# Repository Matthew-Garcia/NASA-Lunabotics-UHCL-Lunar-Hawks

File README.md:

> **New simulation review branch:** [Full rover CAD, Gazebo/RViz launch and KiCad Rev C](docs/SIMULATION_REVIEW.md). Reference-derived geometry; runtime and electrical review remain pending.

# NASA Lunabotics · UHCL Lunar Hawks

### Proof-of-concept lunar excavation rover
Embedded systems · ROS 2 · micro-ROS · OpenCV · LiDAR · Gazebo · Hardware integration

A University of Houston–Clear Lake student and research rover project for lunar-regolith excavation, collection, transportation, and disposal.

This repository brings together the Lunar Hawks rover's ESP32 firmware, NVIDIA Jetson ROS 2 software, micro-ROS communication, mechanical models, electrical documentation, Gazebo simulation assets, and ongoing autonomous-navigation development.

**Status: prototype / research.** Physical rover subsystems have been demonstrated, while the newly added autonomous mission software and simulation environment remain development implementations requiring integration and validation on the physical rover.

This is a team-member-maintained academic/research repository and is **not a NASA-owned or NASA-endorsed software release**.

[ROS 2](ros2_ws/README.md) ·
[micro-ROS](firmware/micro_ros/README.md) ·
[MicroPython](firmware/micropython/README.md) ·
[Autonomy](ros2_ws/src/lunabotics_autonomy/) ·
[Gazebo Simulation](simulation/) ·
[CAD](cad/) ·
[Control PCB](hardware/rover_control_pcb/README.md) ·
[Research](docs/publication/README.md) ·
[Testing](docs/testing/README.md)

---

## Project objectives

The Lunar Hawks rover is being developed as a proof-of-concept robotic platform for lunar excavation research.

The overall mission architecture is intended to support:

1. Entering a simulated or competition excavation environment.
2. Navigating using LiDAR and camera sensing.
3. Identifying traversable regolith terrain.
4. Operating the front bucket-ladder / conveyor excavation mechanism.
5. Transporting collected material.
6. Detecting the disposal area using computer vision.
7. Identifying the four goal-post features surrounding the disposal zone.
8. Aligning the rover with the goal.
9. Activating the disposal bucket.
10. Returning to navigation or excavation behavior.

The current autonomous software is a development baseline rather than a fully validated competition autonomy stack.

---

## Demonstration and evidence

[Watch the archived Gazebo simulation clip](media/Gazebo_Sim.mp4) ·
[Original software documentation](docs/legacy/UHCL_NASA_Lunabotics_Rover_Software_Documentation.pdf)

The physical rover project has demonstrated subsystem functionality including:

- Forward and reverse mobility
- Differential-drive turning
- Wireless teleoperation
- Conveyor / bucket-ladder operation
- Material transportation
- Disposal-bucket actuation
- Jetson-to-ESP32 communication
- micro-ROS integration
- LiDAR integration
- Camera integration

These historical demonstrations do **not** automatically validate the newly added autonomy, Gazebo, CAD, or electrical-development files.

Physical test videos, measured results, software revisions, and dated validation records should continue to be added to the [testing evidence register](docs/testing/README.md).

| Area | Included here | Verification status |
| --- | --- | --- |
| ESP32 micro-ROS | Original C firmware and integration metadata | Preserved project source; hardware revalidation recommended |
| Jetson ROS 2 | Teleoperation and controller software | Existing architecture; environment validation ongoing |
| OpenCV vision | Goal-post and regolith detection nodes | Development baseline; physical threshold tuning required |
| LiDAR autonomy | Front-obstacle safety node | Implemented baseline; rover testing required |
| Mission control | Autonomous excavation/transport/disposal state machine | Implemented baseline; not yet a demonstrated full autonomous mission |
| Gazebo simulation | Lunabotics arena world and rover model | Source added; integrated launch and runtime validation still required |
| Mechanical CAD | Original rover STLs plus autonomy-development CAD | New models are reference/development geometry |
| Rover wheel | 304.8 mm × 100 mm conceptual wheel with 12 grousers | Parametric recreation; hub dimensions must be verified before fabrication |
| Rover control PCB | Routed 4-layer KiCad 9 ESP32/CAN design with USB programming and safety/inhibit logic | ERC/DRC clean; pending fabrication and bring-up |
| Electrical Rev B | Architecture recommendations and schematic review | Engineering-development documentation |
| Research | Manuscript/project documentation | Research publication workflow ongoing |

---

# System architecture

```mermaid
flowchart TD

    Controller["Xbox / Game Controller"] --> Jetson["NVIDIA Jetson Orin NX"]

    Camera["RGB / Depth Camera"] --> Jetson
    Lidar["RPLIDAR"] --> Jetson

    Jetson --> ROS["ROS 2 Humble"]

    ROS --> Teleop["Teleoperation"]
    ROS --> Vision["OpenCV Perception"]
    ROS --> Navigation["Navigation / Mission Logic"]
    ROS --> Safety["LiDAR Safety"]

    Vision --> Mission["Autonomous Mission Manager"]
    Navigation --> Mission
    Safety --> Mission

    Mission --> CMD["/cmd_vel"]
    Teleop --> CMD

    CMD --> Agent["micro-ROS Agent"]

    Agent -->|"UART 115200"| ESP32["ESP32"]

    ESP32 --> WheelDrivers["Wheel Motor Controllers"]
    ESP32 --> Excavator["Excavation Actuators"]
    ESP32 --> Dump["Disposal Bucket Actuators"]

    WheelDrivers --> Wheels["Four Drive Motors"]
    Excavator --> Conveyor["Bucket-Ladder / Conveyor"]
    Dump --> Bucket["Regolith Disposal Bucket"]
```

The architecture separates high-level robotics computation from low-level actuator control.

### NVIDIA Jetson

The Jetson is responsible for higher-level robotics functions such as:

- ROS 2
- Computer vision
- LiDAR processing
- Mapping and localization
- Navigation
- Mission coordination
- Future autonomous excavation behavior

### ESP32

The ESP32 provides hardware-facing embedded control including:

- Motor command generation
- PWM
- Direction control
- Actuator control
- micro-ROS communication
- Hardware safety behavior

The deployed ESP32-WROOM implementation and any future ESP32-S3 control PCB should **not be assumed to be pin-compatible or firmware-compatible without verification**.

---

# Autonomous mission development

The repository now contains an experimental ROS 2 autonomy package:

```text
ros2_ws/src/lunabotics_autonomy/
```

Major nodes include:

### Goal-post detector

```text
goal_post_detector.py
```

Uses OpenCV image processing to locate vertical goal-post candidates from the camera stream.

Publishes goal information that can be used to center the rover between the visible posts.

Development topics include:

```text
/vision/goal_posts/target
/vision/goal_posts/count
/vision/goal_posts/debug
```

The current detector uses configurable image-processing thresholds intended primarily as a simulation and development baseline.

---

### Regolith detector

```text
regolith_detector.py
```

Provides a preliminary OpenCV terrain-classification method for identifying regolith-like regions.

The current implementation is intentionally simple and should eventually be replaced or supplemented with perception trained and tested using representative lunar-regolith imagery.

---

### LiDAR safety

```text
lidar_safety.py
```

Processes `/scan` data and monitors the forward sector of the rover.

It can issue an obstacle-stop condition if an object is detected inside the configured safety distance.

Example topics:

```text
/safety/obstacle_stop
/safety/front_clearance
```

---

### Mission manager

```text
mission_manager.py
```

Implements a development state machine:

```text
ENTER
  ↓
SEARCH_REGOLITH
  ↓
EXCAVATE
  ↓
SEARCH_GOAL
  ↓
ALIGN_GOAL
  ↓
DUMP
  ↓
DONE
```

The mission manager can command:

```text
/cmd_vel
/excavator/enable
/bucket/dump
```

These outputs are intended to eventually interface with the existing ESP32 / micro-ROS hardware layer.

---

# Gazebo simulation

A Lunabotics-inspired Gazebo development environment is included under:

```text
simulation/worlds/
```

Current world:

```text
lunabotics_arena.world
```

The environment contains:

- Excavation terrain
- Arena boundaries
- Disposal region
- Four visual goal posts
- A simplified mission layout

The environment is a **development approximation**, not a claim of exact NASA competition-field dimensions.

A simplified rover model is also included:

```text
ros2_ws/src/lunabotics_description/urdf/lunabotics_rover.urdf.xacro
```

It represents:

- Four-wheel differential drive
- Rover chassis
- Front excavation conveyor
- Rear disposal bucket
- LiDAR
- RGB camera

An integrated Gazebo spawn/bringup launch file is still planned.

*Lunar Hawks rover simulation with grouser wheels, a scoop conveyor excavator, and an actuator-driven disposal bucket. Full autonomous excavation and disposal remain under development.*

---

# Computer vision

The autonomy software uses OpenCV as a development perception layer.

Current objectives include:

```text
Camera
   ↓
OpenCV
   ↓
Goal-post detection
   ↓
Four-post confirmation
   ↓
Goal-center calculation
   ↓
Rover alignment
   ↓
Dump sequence
```

Future work may combine camera information with LiDAR geometry for more robust goal detection and navigation.

---

# LiDAR navigation

LiDAR provides the geometric sensing layer for autonomous rover development.

Planned progression:

```text
LiDAR
  ↓
Obstacle detection
  ↓
Localization
  ↓
Mapping
  ↓
Nav2 costmaps
  ↓
Waypoint navigation
  ↓
Mission navigation
```

Future integration is expected to include ROS 2 Nav2 and/or SLAM Toolbox.

---

# Mechanical development

The repository includes both preserved project CAD and new development geometry.

```text
cad/
```

The original supplied meshes remain directly in `cad/`. Generated geometry is separated by purpose:

```text
cad/
├── original supplied STL files
├── full_rover/
│   ├── chassis, bucket and excavator parts
│   ├── ESP32 and Jetson enclosures
│   └── 248 mm and 300 mm wheel variants
└── autonomy_rover/
    ├── goal_post.scad / .stl
    ├── grouser_wheel_12_short.scad / .stl
    └── rover_chassis_simplified.scad / .stl
```

The full-rover wheel set and printable cover variants are documented in [`cad/full_rover/WHEEL.md`](cad/full_rover/WHEEL.md).

## Grouser wheel

The development wheel is based on documented rover dimensions:

- Diameter: **304.8 mm**
- Width: **100 mm**
- Grousers: **12**
- Equal angular spacing: **30°**

The grouser projection in this development model was shortened relative to the initial generated geometry.

The wheel STL is **not fabrication-authoritative**. Hub diameter, shaft bore, bolt-circle dimensions, materials, tolerances, and drivetrain interfaces must be verified against the physical rover.

---

# Electrical architecture

The rover uses separated high-current motor and computing power domains.

```mermaid
flowchart TD

    BAT24["24 V Battery"] --> Fuse["Main Fuse"]
    Fuse --> Estop["Latching E-Stop / Contactor"]
    Estop --> Dist["Fused 24 V Distribution"]

    Dist --> FL["Front Left Motor Controller"]
    Dist --> FR["Front Right Motor Controller"]
    Dist --> RL["Rear Left Motor Controller"]
    Dist --> RR["Rear Right Motor Controller"]
    Dist --> EX["Excavator / Conveyor"]
    Dist --> ACT["Linear Actuators"]

    VMOUNT["V-Mount Compute Battery"] --> JetsonFuse["Compute Fuse / Protection"]
    JetsonFuse --> Jetson["Jetson Orin NX"]

    Logic["Regulated Logic Rail"] --> ESP32["ESP32"]
    Logic --> Sensors["Low-Voltage Sensors"]

    Jetson <-->|"UART / micro-ROS"| ESP32
```

Rev-B design recommendations are located in:

```text
docs/electrical/rev_b/
```

They include:

- Main battery protection
- Branch fusing
- Emergency-stop architecture
- Transient suppression
- Power-domain separation
- Logic-rail decoupling
- UART signal protection
- Test points
- Current-monitoring recommendations
- Motor-controller schematic review

One important design-review item is ensuring that schematic symbols and labels accurately represent the physical motor controllers being used.

---

# Start with software-only checks

Clone the repository:

```bash
git clone https://github.com/Matthew-Garcia/NASA-Lunabotics-UHCL-Lunar-Hawks.git

cd NASA-Lunabotics-UHCL-Lunar-Hawks
```

Run MicroPython protocol tests:

```bash
python3 firmware/micropython/test.py
```

Run repository tests:

```bash
python3 -m unittest discover -s tests -v
```

For ROS 2 setup, see:

[ROS 2 workspace instructions](ros2_ws/README.md)

For micro-ROS integration:

[micro-ROS notes](firmware/micro_ros/README.md)

Before powering physical motors or actuators:

[Electrical safety checklist](docs/electrical/SAFETY.md)

---

# Repository map

| Path | Purpose |
| --- | --- |
| `firmware/micro_ros/` | ESP32 C / micro-ROS firmware |
| `firmware/micropython/` | MicroPython communication prototype |
| `ros2_ws/src/lunabotics_teleop/` | ROS 2 controller and teleoperation package |
| `ros2_ws/src/lunabotics_autonomy/` | OpenCV, LiDAR, and autonomous mission development |
| `ros2_ws/src/lunabotics_description/` | Rover URDF/Xacro description |
| `simulation/worlds/` | Gazebo Lunabotics arena |
| `hardware/rover_control_pcb/` | Proposed rover-control/interface PCB |
| `cad/` | Mechanical models and original STL files |
| `cad/full_rover/` | Full rover reconstruction, excavator, bucket, enclosures and wheel variants |
| `cad/autonomy_rover/` | Earlier simplified autonomy-development CAD and goal-post geometry |
| `docs/architecture/` | Interfaces, command semantics, and system architecture |
| `docs/electrical/` | Electrical safety and architecture documentation |
| `docs/electrical/rev_b/` | Rev-B electrical recommendations and schematic review |
| `docs/testing/` | Evidence register and validation planning |
| `docs/publication/` | Research publication status |
| `docs/legacy/` | Original software documentation |
| `media/` | Rover images, team media, and Gazebo video |
| `tests/` | Host-side software tests |

---

# Development roadmap

- [x] Integrate Jetson and ESP32 architecture.
- [x] Establish ROS 2 teleoperation.
- [x] Establish micro-ROS communication.
- [x] Integrate LiDAR hardware.
- [x] Integrate camera hardware.
- [x] Demonstrate rover mobility.
- [x] Demonstrate excavation conveyor operation.
- [x] Demonstrate disposal-bucket actuation.
- [x] Add OpenCV goal-post detection baseline.
- [x] Add regolith-vision development node.
- [x] Add LiDAR obstacle-safety node.
- [x] Add autonomous mission state-machine baseline.
- [x] Add Gazebo Lunabotics arena source.
- [x] Add simplified rover URDF/Xacro.
- [x] Add 12-grouser wheel development CAD.
- [x] Add Rev-B electrical architecture review.
- [ ] Complete ROS package for rover description and Gazebo spawning.
- [ ] Add combined simulation launch file.
- [ ] Integrate ROS 2 Nav2.
- [ ] Integrate SLAM / localization.
- [ ] Fuse camera and LiDAR perception.
- [ ] Validate four-post detection using representative physical targets.
- [ ] Validate autonomous navigation on the physical rover.
- [ ] Integrate autonomous excavation control with ESP32 firmware.
- [ ] Implement mission recovery and watchdog behavior.
- [ ] Record quantitative excavation and navigation results.
- [ ] Complete and independently review production PCB schematic/layout.
- [ ] Demonstrate a complete autonomous excavation → transport → disposal mission.

---

# Research

**Matthew Garcia**  
Repository maintainer · Robotics systems integration · Embedded systems · ROS 2 / autonomy contributor · Co-Author

**Dr. Luong Nguyen, Ph.D.**  
Research adviser · Lead-Author

Credit also belongs to the **University of Houston–Clear Lake Lunar Hawks team** and the students who designed, built, tested, and improved the rover platform.

Research project:

*Design and Implementation of a Proof-of-Concept Excavating Rover Platform for Lunar Regolith Collection and Transportation*

The project has been accepted for presentation at **ISMCR 2026 — International Symposium on Measurement and Control in Robotics**.

Research documentation and publication status are maintained under:

[Read the author manuscript (Word)](docs/publication/manuscript/Nguyen_Garcia_ISMCR2026_Final_Revision.docx) · [Publication status](docs/publication/README.md)

---

## Links

[Matthew Garcia Portfolio](https://matthew-garcia-portfolio.vercel.app/) ·
[LinkedIn](https://www.linkedin.com/in/matthew-garcia-165634195/) ·
[Original UHCL Lunar Hawks Repository](https://github.com/Matthew-Garcia/uhcl-lunar-hawks-lunabotics)

---

# Safety

This repository contains software and design material capable of controlling motors and electromechanical actuators.

Do not connect development software directly to powered hardware without verifying:

- Emergency stop functionality
- Motor-controller pin assignments
- PWM ranges
- Direction logic
- Current limits
- Fuse ratings
- Mechanical clearance
- Command timeout behavior
- Communication-loss behavior

See:

[Electrical Safety](docs/electrical/SAFETY.md)

---

# License and provenance

The original MIT license is retained.

See [NOTICE](NOTICE.md) for source revision, provenance, and rights information.

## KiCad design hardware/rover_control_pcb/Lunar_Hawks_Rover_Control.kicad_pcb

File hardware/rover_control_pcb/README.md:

# NASA Lunabotics — UHCL Lunar Hawks Low-Level Embedded Control & I/O PCB

**Native KiCad 9.0 rover-control hardware design** for the University of Houston–Clear Lake Lunar Hawks Lunabotics rover.

This board is the rover's **low-level embedded control and I/O PCB**. The NVIDIA Jetson Orin NX remains the high-level ROS 2/autonomy computer, while this PCB handles the hardware-facing embedded layer: ESP32 control, CAN communication, programming/service I/O, safety/inhibit logic, and command interfaces to external wheel and mechanism drivers.

> **Engineering draft — not released for fabrication or powered operation.** ERC/DRC results establish design-file consistency, not electrical, thermal, RF, EMC, harness, or safety qualification.

## Designed in KiCad 9.0

The controller is designed and maintained **natively in KiCad 9.0**. The current design snapshot was validated with the KiCad 9 toolchain.

The KiCad project includes the project file, hierarchical schematic sheets, routed PCB layout, local symbol resources, 3D-model support, board artwork, BOM/component records, placement data, layout notes, and electrical validation reports.

## Rover control hierarchy

```text
NVIDIA Jetson Orin NX
High-level ROS 2 / autonomy / perception / planning
                 |
                 | CAN / system interface
                 v
LOW-LEVEL EMBEDDED CONTROL & I/O PCB
ESP32 / safety logic / command generation / hardware I/O
                 |
                 v
External motor drivers / actuators / excavation / disposal
```

The board silkscreen identifies the design as:

- **NASA LUNABOTICS — UHCL LUNAR HAWKS**
- **LOW-LEVEL EMBEDDED CONTROL & I/O PCB**
- **CONTROL SIGNALS ONLY — NO MOTOR POWER**

## Current board

- 160 × 100 mm working outline
- four copper layers
- blue solder mask / white silkscreen configuration
- ESP32-WROOM-32E-N4 embedded controller module
- USB-C programming/service interface
- Classical CAN interface with two parallel connectors and selectable 120 Ω termination
- four external BLDC wheel-driver command interfaces
- external linear-actuator / excavation / deployment / disposal command interfaces
- protected controller power conversion to 5 V and 3.3 V rails
- watchdog, re-arm, command-enable, and inhibit logic
- provisional wheel-stop request interfaces
- system/status indicators and service headers
- four mounting holes and Lunar Hawks board artwork
- **motor-current paths remain external to the PCB**

## Architecture notes

**Embedded controller:** the ESP32 provides the low-level hardware-control layer. Manual BOOT/reset support and the USB programming path are integrated on the board.

**CAN:** the controller-side CAN node includes the transceiver, protection, parallel bus connectors, and selectable termination. The Jetson requires its own appropriate CAN transceiver/adapter; logic-level CAN signals are not connected directly to CAN_H/CAN_L.

**Driver interfaces:** motor power is intentionally external. This PCB supplies command/control interfaces to the external wheel and rover-mechanism driver hardware.

**Safety/inhibit layer:** low-voltage interlock, watchdog, arm/re-arm, and command-inhibit functions are included. This PCB is not a safety-rated high-current disconnect; the rover's high-current emergency power interruption remains external.

## Board previews

### 3D board render

### Top view

### Front PCB layout

## Open the project

Open `Lunar_Hawks_Rover_Control.kicad_pro` in KiCad 9 with the standard KiCad symbol, footprint, and 3D-model libraries installed. Keep all child schematics, `Rover.kicad_sym`, `sym-lib-table`, and the `3dmodels` folder together. The corrected ESP32-WROOM-32E model is bundled and referenced using `${KIPRJMOD}`; other component models use standard KiCad libraries. The artwork is embedded in the PCB and the source image is preserved in `artwork/`.

## Current design

- 160 × 100 mm, four copper layers, blue solder mask and white silkscreen.
- Soldered ESP32-WROOM-32E-N4 module with integrated antenna; USB-C programming and Classical CAN interface.
- Interfaces for four external BLDC drivers, four external linear-actuator drivers, and one external excavator driver.
- Controller power conversion, status LEDs, watchdog/re-arm logic, and provisional wheel-stop interfaces.
- 201 schematic components: 186 populated and 15 DNP. Four mounting-hole footprints and two board-only logo footprints are additional, for 207 footprints total.
- 23 mm front logo and 48 mm rear logo. Their fine details require fabricator silkscreen capability review.
- Motor-current paths remain external to this controller PCB.

The preview uses white/light-blue trace colors for readability; these are display colors. The native PCB defines the manufacturing layers.

## Validation snapshot — September 16, 2026

KiCad 9.0.4 was run on this board with both logos, all-track-error reporting, schematic parity, and all severities including exclusions:

| Check | Result |
| --- | ---: |
| PCB DRC violations | 0 |
| Unconnected PCB items | 0 |
| Schematic/PCB parity issues | 0 |
| Schematic ERC errors | 0 |
| Schematic ERC warnings | 0 |

Reports: [PCB DRC](validation/PCB_Both_Logos_DRC.json), [schematic ERC](validation/Schematic_Both_Logos_ERC.rpt), and [layout status](validation/PCB_Layout_Status.json).

## BOM and design documentation

- [Grouped draft BOM](bom/BOM.md) and [individual component records](bom/BOM_Components.json). Exact ordering codes still marked TBD must be selected and verified before purchase.
- [Physical layout notes](docs/PCB_Layout_Notes.md), [power design](docs/Power_Design.md), [driver interfaces](docs/Driver_Interfaces.md), [interlock design](docs/Safety_And_Driver_Design.md), and [wheel-stop interfaces](docs/Wheel_Stop_Design.md).
- [Hardware requirements](docs/Hardware_Requirements.md) and [detailed design notes](docs/Design_Notes.md).
- `data/PCB_Placement.csv` is a draft position inventory of the 201 circuit components and four mounting holes; artwork is excluded. It is not a released assembly pick-and-place file.

## Remaining engineering review

Review power-converter current paths and thermal behavior, USB routing, ESP32 footprint and antenna clearance, exact component packages, connector pinouts/control levels, mounting dimensions, and the manufacturing stackup. Resolve the external E-stop DC interruption rating and J301 dry-contact permissive wiring; qualify DNP driver links. Sensor/end-limit circuits, paired-actuator synchronization, firmware, and hardware testing remain outstanding. The sensor sheet is a placeholder. No manufacturing Gerber/drill release is included.

## Rear PCB artwork

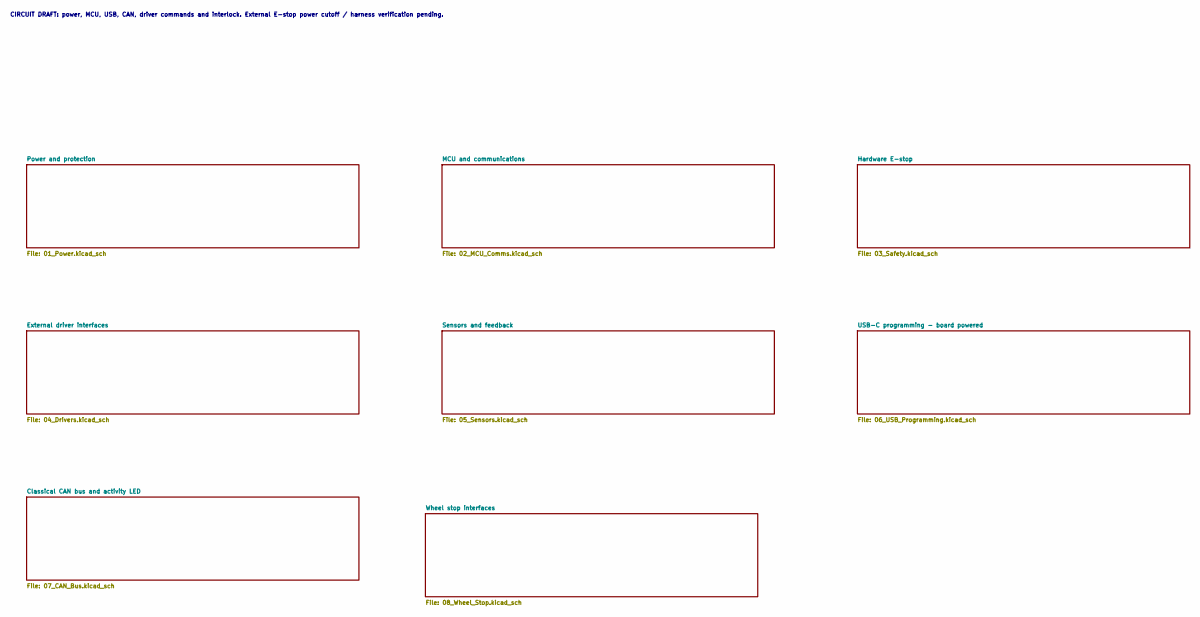
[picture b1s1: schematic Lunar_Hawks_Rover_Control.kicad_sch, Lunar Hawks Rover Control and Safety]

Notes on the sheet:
CIRCUIT DRAFT: power, MCU, USB, CAN, driver commands and interlock. External E-stop power cutoff / harness verification pending.

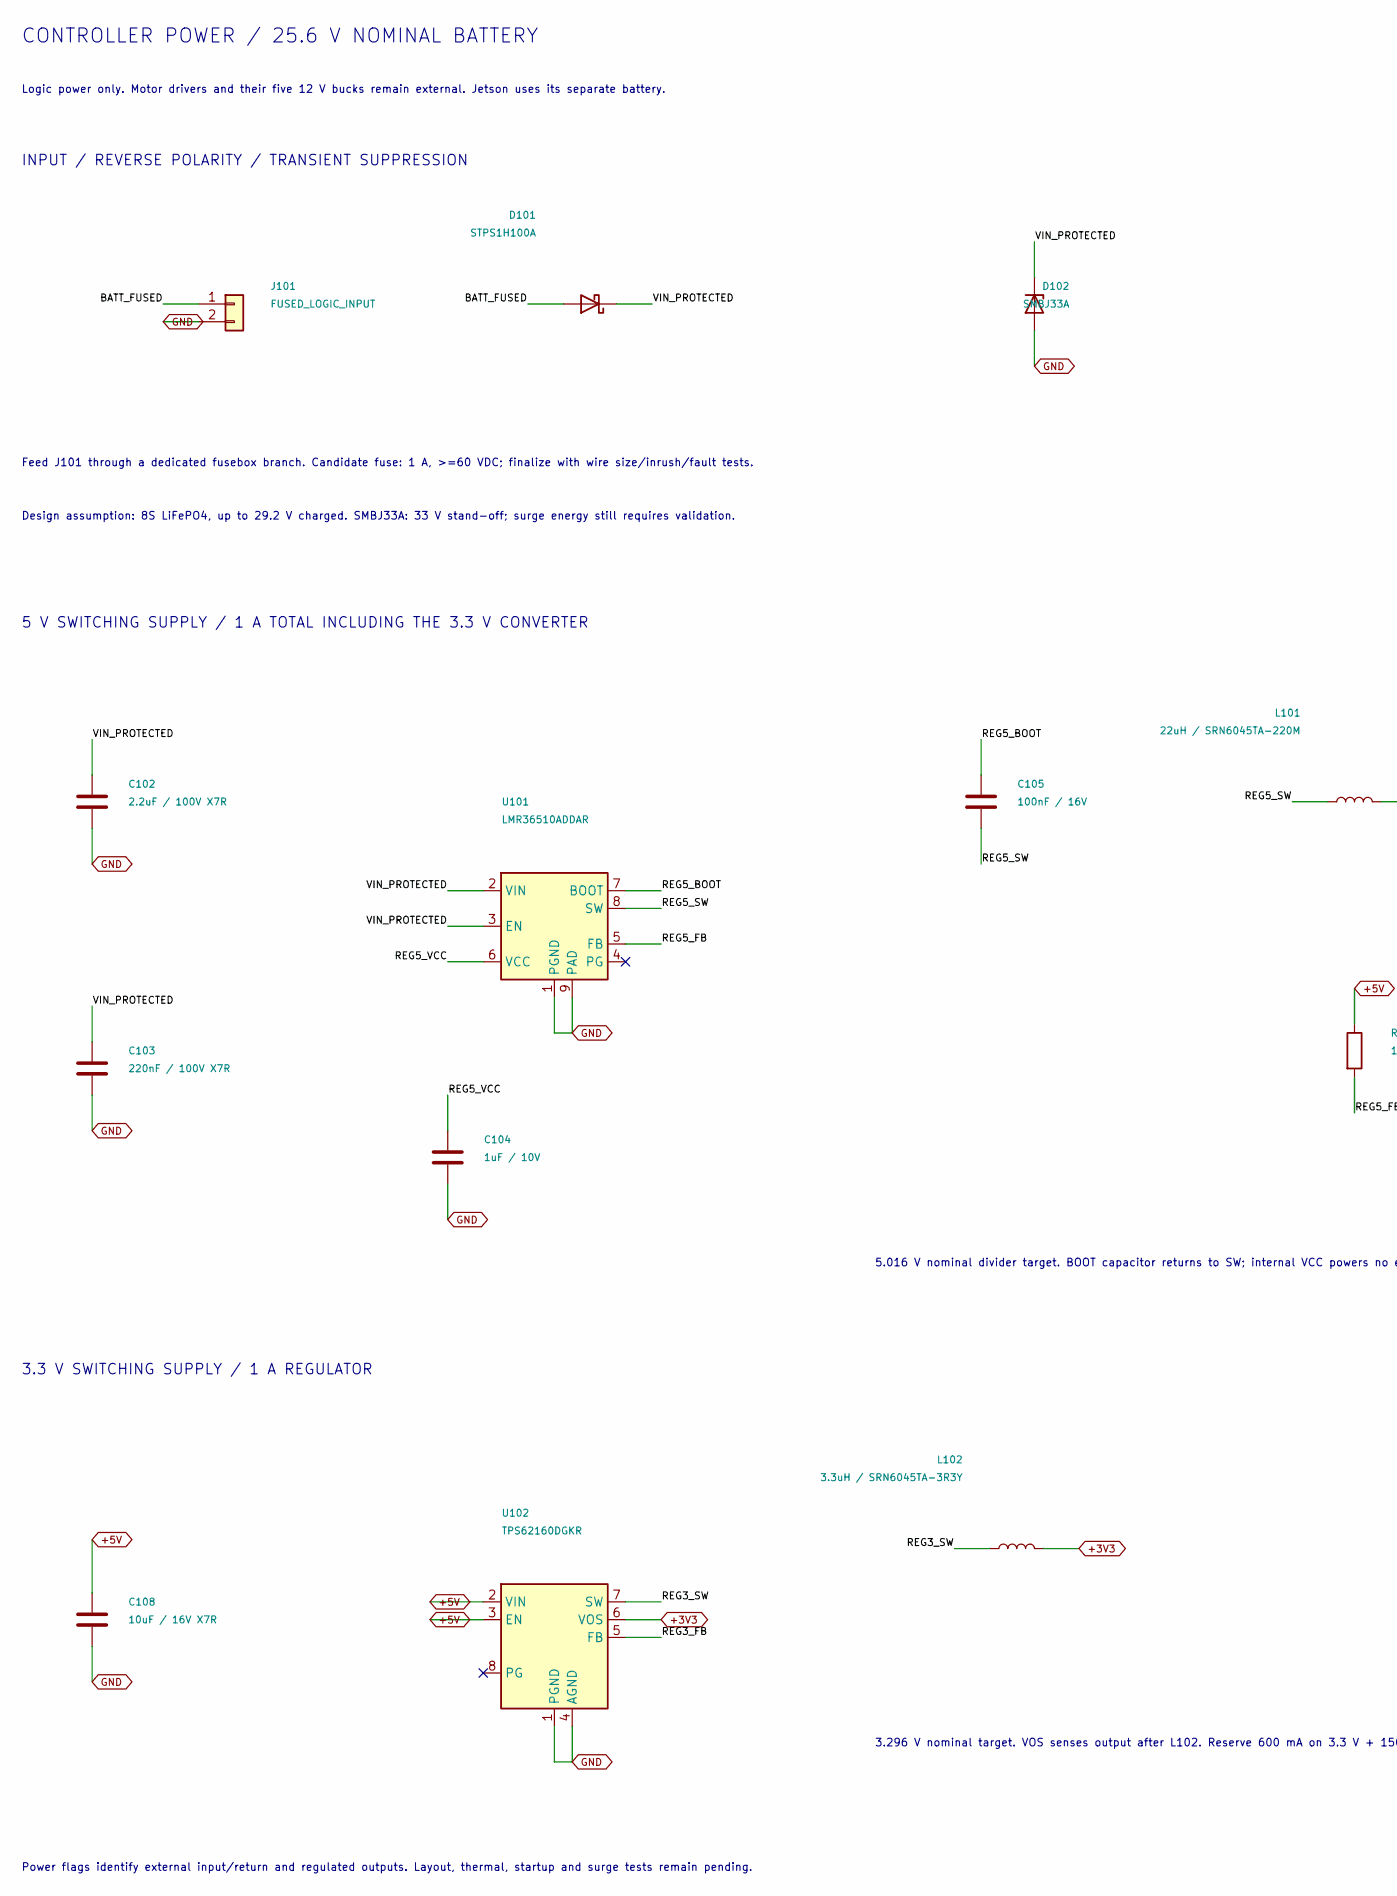
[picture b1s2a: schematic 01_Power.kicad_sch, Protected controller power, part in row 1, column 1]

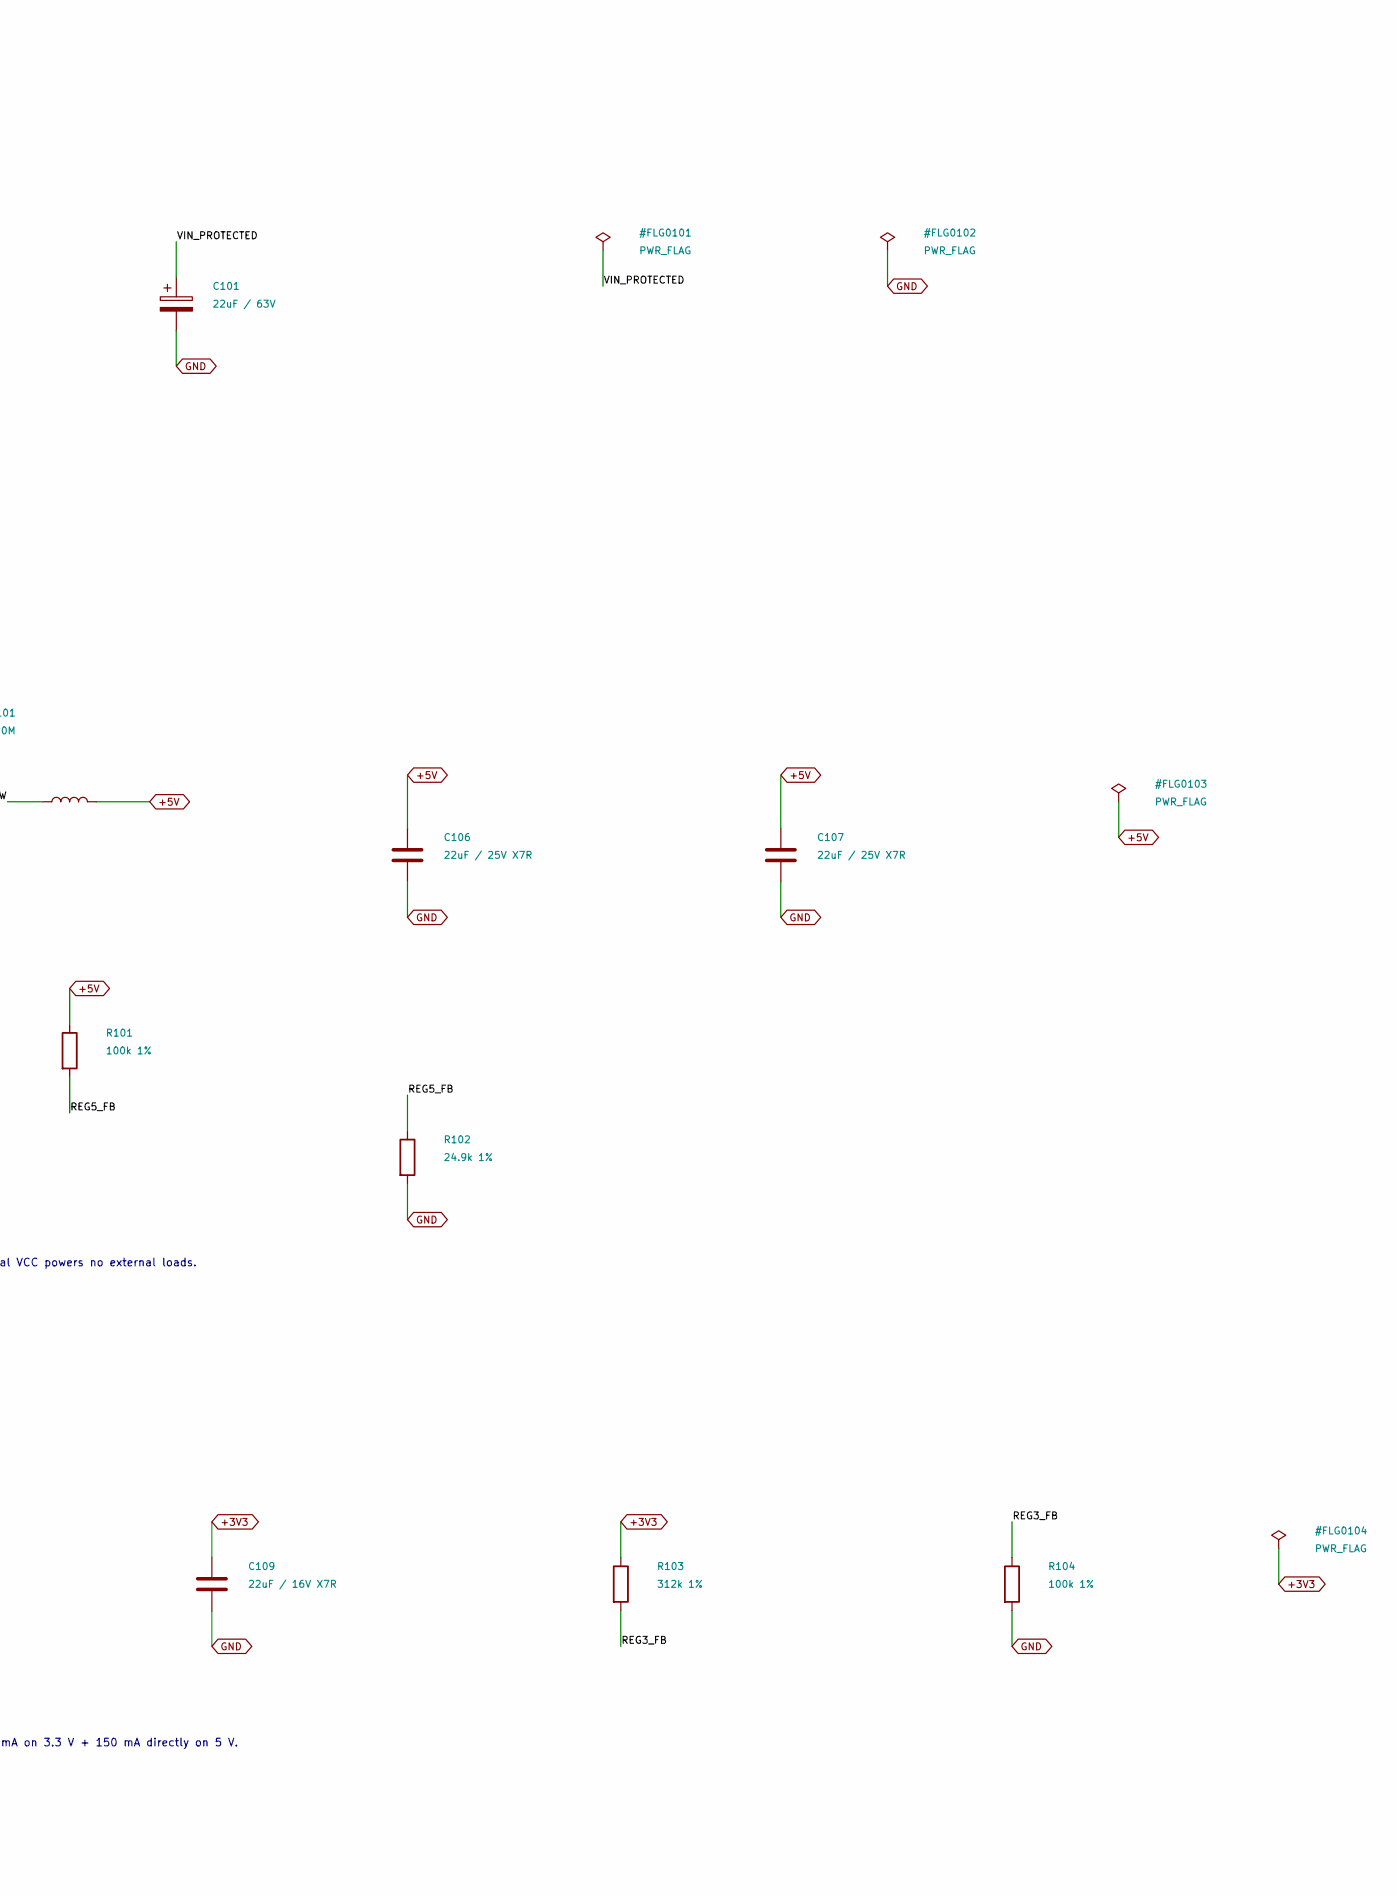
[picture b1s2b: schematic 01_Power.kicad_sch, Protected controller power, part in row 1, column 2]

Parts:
C101: 22uF / 63V; CP_Radial_D8.0mm_P3.50mm
C102: 2.2uF / 100V X7R; C_1210_3225Metric
C103: 220nF / 100V X7R; C_0805_2012Metric
C104: 1uF / 10V; C_0805_2012Metric
C105: 100nF / 16V; C_0805_2012Metric
C106, C107: 22uF / 25V X7R; C_1210_3225Metric
C108: 10uF / 16V X7R; C_0805_2012Metric
C109: 22uF / 16V X7R; C_1206_3216Metric
D101: STPS1H100A; D_SMA
D102: SMBJ33A; D_SMB
J101: FUSED_LOGIC_INPUT; TerminalBlock_Phoenix_MKDS-1,5-2_1x02_P5.00mm_Horizontal
L101: 22uH / SRN6045TA-220M; L_Bourns_SRN6045TA
L102: 3.3uH / SRN6045TA-3R3Y; L_Bourns_SRN6045TA
R101, R104: 100k 1%; R_0603_1608Metric
R102: 24.9k 1%; R_0603_1608Metric
R103: 312k 1%; R_0603_1608Metric
U101: LMR36510ADDAR; Texas_HTSOP-8-1EP_3.9x4.9mm_P1.27mm_EP2.95x4.9mm_Mask2.4x3.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
U102: TPS62160DGKR; MSOP-8_3x3mm_P0.65mm

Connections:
+3V3: C109.1, L102.2, R103.1, U102.6 (VOS); also elsewhere on the board
+5V: C106.1, C107.1, C108.1, L101.2, R101.1, U102.2 (VIN), U102.3 (EN); also elsewhere on the board
/Power and protection/BATT_FUSED: D101.2 (A), J101.1
/Power and protection/REG3_FB: R103.2, R104.1, U102.5 (FB)
/Power and protection/REG3_SW: L102.1, U102.7 (SW)
/Power and protection/REG5_BOOT: C105.1, U101.7 (BOOT)
/Power and protection/REG5_FB: R101.2, R102.1, U101.5 (FB)
/Power and protection/REG5_SW: C105.2, L101.1, U101.8 (SW)
/Power and protection/REG5_VCC: C104.1, U101.6 (VCC)
/Power and protection/VIN_PROTECTED: C101.1, C102.1, C103.1, D101.1 (K), D102.1 (K), U101.2 (VIN), U101.3 (EN)
GND: C101.2, C102.2, C103.2, C104.2, C106.2, C107.2, C108.2, C109.2, D102.2 (A), J101.2, R102.2, R104.2, U101.1 (PGND), U101.9 (PAD), U102.1 (PGND), U102.4 (AGND); also elsewhere on the board

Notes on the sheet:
CONTROLLER POWER / 25.6 V NOMINAL BATTERY
Logic power only. Motor drivers and their five 12 V bucks remain external. Jetson uses its separate battery.
INPUT / REVERSE POLARITY / TRANSIENT SUPPRESSION
Feed J101 through a dedicated fusebox branch. Candidate fuse: 1 A, >=60 VDC; finalize with wire size/inrush/fault tests.
Design assumption: 8S LiFePO4, up to 29.2 V charged. SMBJ33A: 33 V stand-off; surge energy still requires validation.
5 V SWITCHING SUPPLY / 1 A TOTAL INCLUDING THE 3.3 V CONVERTER
5.016 V nominal divider target. BOOT capacitor returns to SW; internal VCC powers no external loads.
3.3 V SWITCHING SUPPLY / 1 A REGULATOR
3.296 V nominal target. VOS senses output after L102. Reserve 600 mA on 3.3 V + 150 mA directly on 5 V.
Power flags identify external input/return and regulated outputs. Layout, thermal, startup and surge tests remain pending.

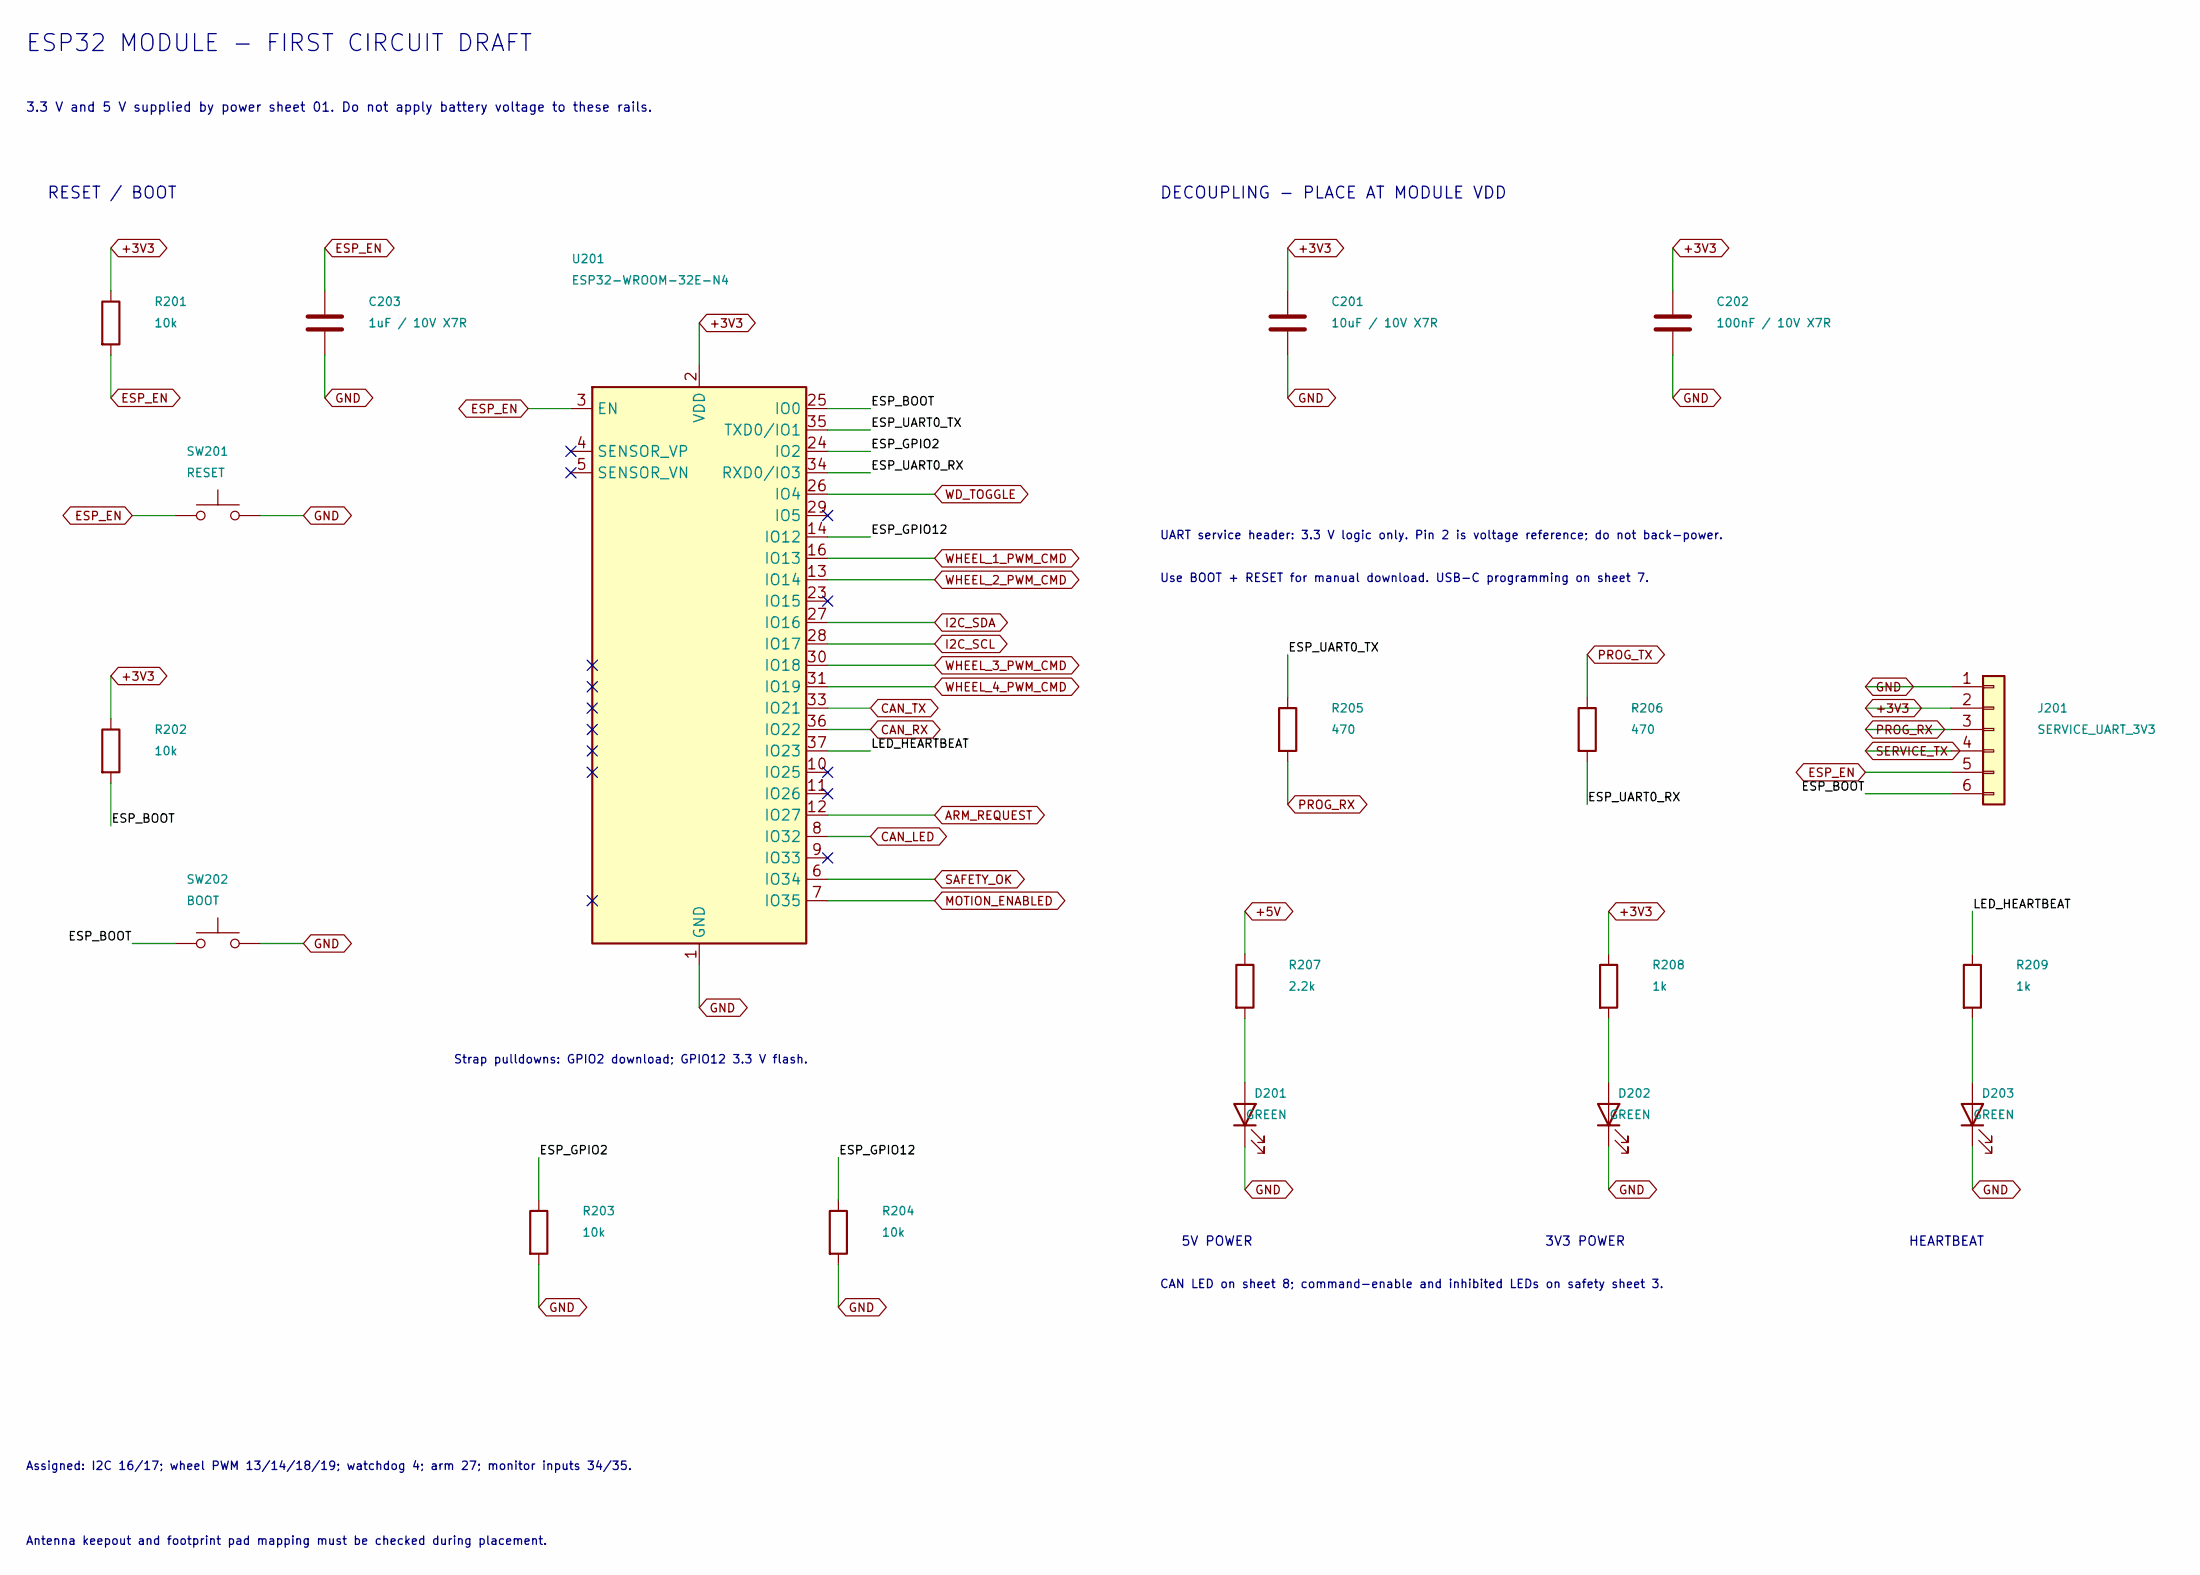
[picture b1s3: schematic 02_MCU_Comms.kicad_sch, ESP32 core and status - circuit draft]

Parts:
C201: 10uF / 10V X7R; C_0805_2012Metric
C202: 100nF / 10V X7R; C_0603_1608Metric
C203: 1uF / 10V X7R; C_0603_1608Metric
D201, D202, D203: GREEN; LED_0603_1608Metric
J201: SERVICE_UART_3V3; PinHeader_1x06_P2.54mm_Vertical
R201, R202, R203, R204: 10k; R_0603_1608Metric
R205, R206: 470; R_0603_1608Metric
R207: 2.2k; R_0603_1608Metric
R208, R209: 1k; R_0603_1608Metric
SW201: RESET; SW_SPST_TL3342
SW202: BOOT; SW_SPST_TL3342
U201: ESP32-WROOM-32E-N4; ESP32-WROOM-32D

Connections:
+3V3: C201.1, C202.1, J201.2, R201.1, R202.1, R208.1, U201.2 (VDD); also elsewhere on the board
+5V: R207.1; also elsewhere on the board
/MCU and communications/ESP_BOOT: J201.6, R202.2, SW202.1, U201.25 (IO0)
/MCU and communications/ESP_GPIO2: R203.1, U201.24 (IO2)
/MCU and communications/ESP_GPIO12: R204.1, U201.14 (IO12)
/MCU and communications/ESP_UART0_RX: R206.2, U201.34 (RXD0/IO3)
/MCU and communications/ESP_UART0_TX: R205.1, U201.35 (TXD0/IO1)
/MCU and communications/LED_HEARTBEAT: R209.1, U201.37 (IO23)
ARM_REQUEST: U201.12 (IO27); also elsewhere on the board
CAN_LED: U201.8 (IO32); also elsewhere on the board
CAN_RX: U201.36 (IO22); also elsewhere on the board
CAN_TX: U201.33 (IO21); also elsewhere on the board
ESP_EN: C203.1, J201.5, R201.2, SW201.1, U201.3 (EN); also elsewhere on the board
GND: C201.2, C202.2, C203.2, D201.1 (K), D202.1 (K), D203.1 (K), J201.1, R203.2, R204.2, SW201.2, SW202.2, U201.1 (GND), U201.15 (GND), U201.38 (GND), U201.39 (GND); also elsewhere on the board
I2C_SCL: U201.28 (IO17); also elsewhere on the board
I2C_SDA: U201.27 (IO16); also elsewhere on the board
MOTION_ENABLED: U201.7 (IO35); also elsewhere on the board
unnamed: D201.2 (A), R207.2
unnamed: D202.2 (A), R208.2
unnamed: D203.2 (A), R209.2
PROG_RX: J201.3, R205.2; also elsewhere on the board
PROG_TX: R206.1; also elsewhere on the board
SAFETY_OK: U201.6 (IO34); also elsewhere on the board
SERVICE_TX: J201.4; also elsewhere on the board
WD_TOGGLE: U201.26 (IO4); also elsewhere on the board
WHEEL_1_PWM_CMD: U201.16 (IO13); also elsewhere on the board
WHEEL_2_PWM_CMD: U201.13 (IO14); also elsewhere on the board
WHEEL_3_PWM_CMD: U201.30 (IO18); also elsewhere on the board
WHEEL_4_PWM_CMD: U201.31 (IO19); also elsewhere on the board

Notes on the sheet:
5V POWER
3V3 POWER
HEARTBEAT
ESP32 MODULE - FIRST CIRCUIT DRAFT
3.3 V and 5 V supplied by power sheet 01. Do not apply battery voltage to these rails.
RESET / BOOT
DECOUPLING - PLACE AT MODULE VDD
UART service header: 3.3 V logic only. Pin 2 is voltage reference; do not back-power.
Use BOOT + RESET for manual download. USB-C programming on sheet 7.
Strap pulldowns: GPIO2 download; GPIO12 3.3 V flash.
Assigned: I2C 16/17; wheel PWM 13/14/18/19; watchdog 4; arm 27; monitor inputs 34/35.
CAN LED on sheet 8; command-enable and inhibited LEDs on safety sheet 3.
Antenna keepout and footprint pad mapping must be checked during placement.
